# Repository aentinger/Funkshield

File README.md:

💾 Funkshield
==============

# 📸 Image

# 📂 Description

The Radio Shield provides an easy way to enable wireless communication between two or more Arduinos. Additionally the Radioshield has a Childboard connector socket which allows the Radio Shield to be further upgraded with sensors/actuators, e.g. a gas sensor, temperature sensor or a relay switch. A possible application would be temperature monitoring of all rooms of a house/appartment and performing an efficient regulation of the heating based on the measured data. For an quick and easy start, a open source Arduino library with sample programs is available.

**Features**

* Enables easy wireless communication with other Arduinos
* Usage of the popular RFM12B HF-Transceiver
* Frequency range: 433 MHz ISM-Band
* Childboard-Base for integration of further LXRobotics Childboards (e.g. gas sensor, temperature sensor, relay switch)
* Antenna with 2dbi gain
* Output power is selectable in 3 db steps ranging from 0 dbm to -21 dbm
* Third-Party-Arduino Library available for control with example programms

# 🎥 [Video](images/funkshield_demo.mp4)

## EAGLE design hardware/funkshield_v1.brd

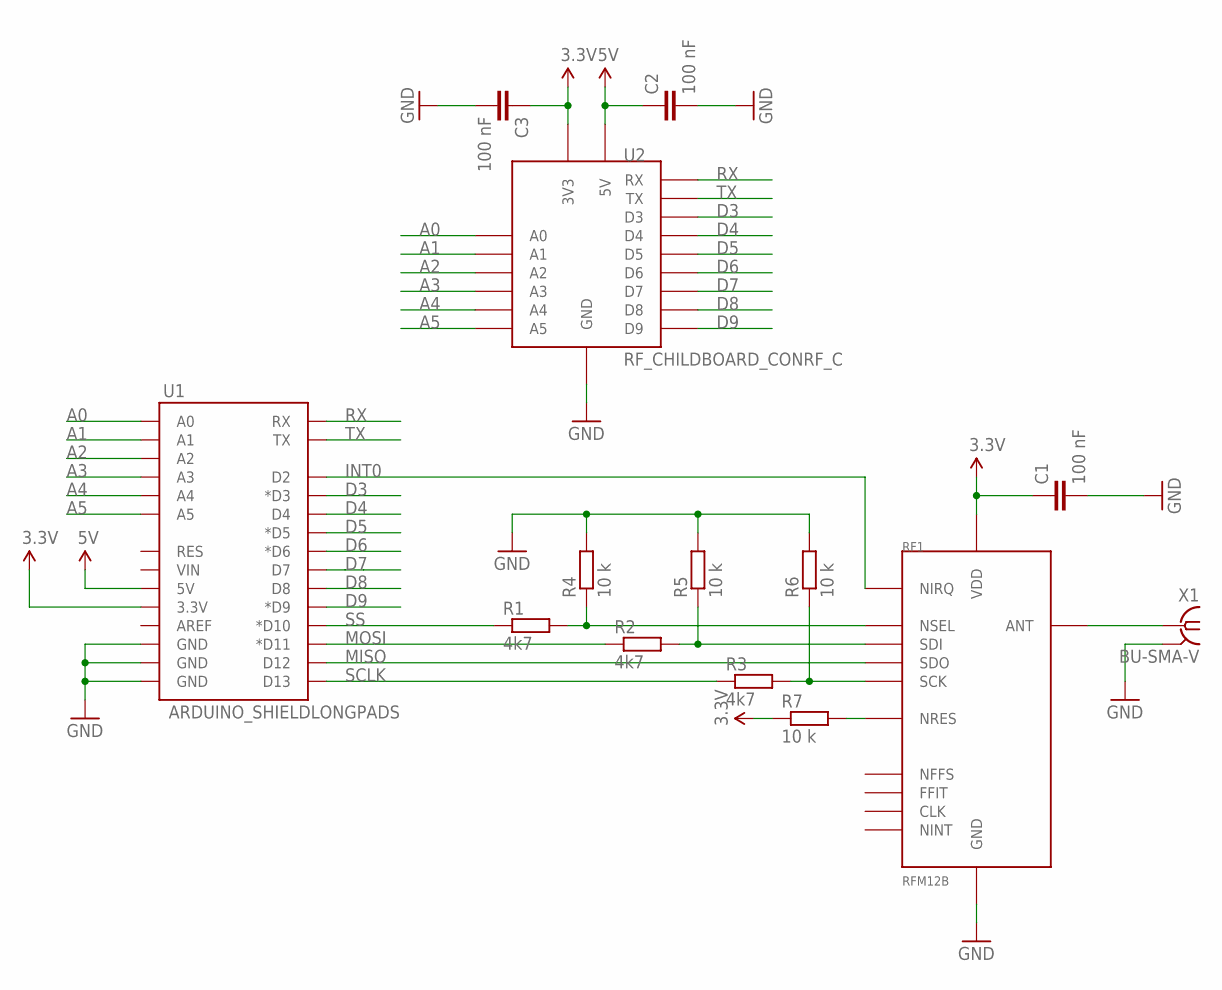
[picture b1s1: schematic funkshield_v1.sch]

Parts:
C1, C2, C3: 100 nF; C0805
R1, R2, R3: 4k7; M0805
R4, R5, R6, R7: 10 k; M0805
RF1: RFM12B
U1: ARDUINO_SHIELDLONGPADS; DUEMILANOVE_SHIELD_LONGPADS
U2: RF_CHILDBOARD_CONRF_C; RF_CHILDBOARD_CON
X1: BU-SMA-V

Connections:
3.3V: C1.1, C3.1, R7.1, RF1.VDD, U1.3.3V, U2.3V3
5V: C2.1, U1.5V, U2.5V
A0: U1.A0, U2.A0
A1: U1.A1, U2.A1
A2: U1.A2, U2.A2
A3: U1.A3, U2.A3
A4: U1.A4, U2.A4
A5: U1.A5, U2.A5
D3: U1.D3 (*D3), U2.D3
D4: U1.D4, U2.D4
D5: U1.D5 (*D5), U2.D5
D6: U1.D6 (*D6), U2.D6
D7: U1.D7, U2.D7
D8: U1.D8, U2.D8
D9: U1.D9 (*D9), U2.D9
GND: C1.2, C2.2, C3.2, R4.2, R5.2, R6.2, RF1.GND, RF1.GND1 (GND), U1.GND@0 (GND), U1.GND@1 (GND), U1.GND@2 (GND), U2.GND, U2.GND1 (GND), U2.GND2 (GND), X1.2 (GND), X1.3 (GND), X1.4 (GND), X1.5 (GND)
INT0: RF1.NIRQ, U1.D2
MISO: RF1.SDO, U1.D12
MOSI: R2.1, U1.D11 (*D11)
unnamed: R1.2, R4.1, RF1.NSEL
unnamed: R2.2, R5.1, RF1.SDI
unnamed: R3.2, R6.1, RF1.SCK
unnamed: R7.2, RF1.NRES
unnamed: RF1.ANT, X1.1
RX: U1.RX, U2.RX
SCLK: R3.1, U1.D13
SS: R1.1, U1.D10 (*D10)
TX: U1.TX, U2.TX

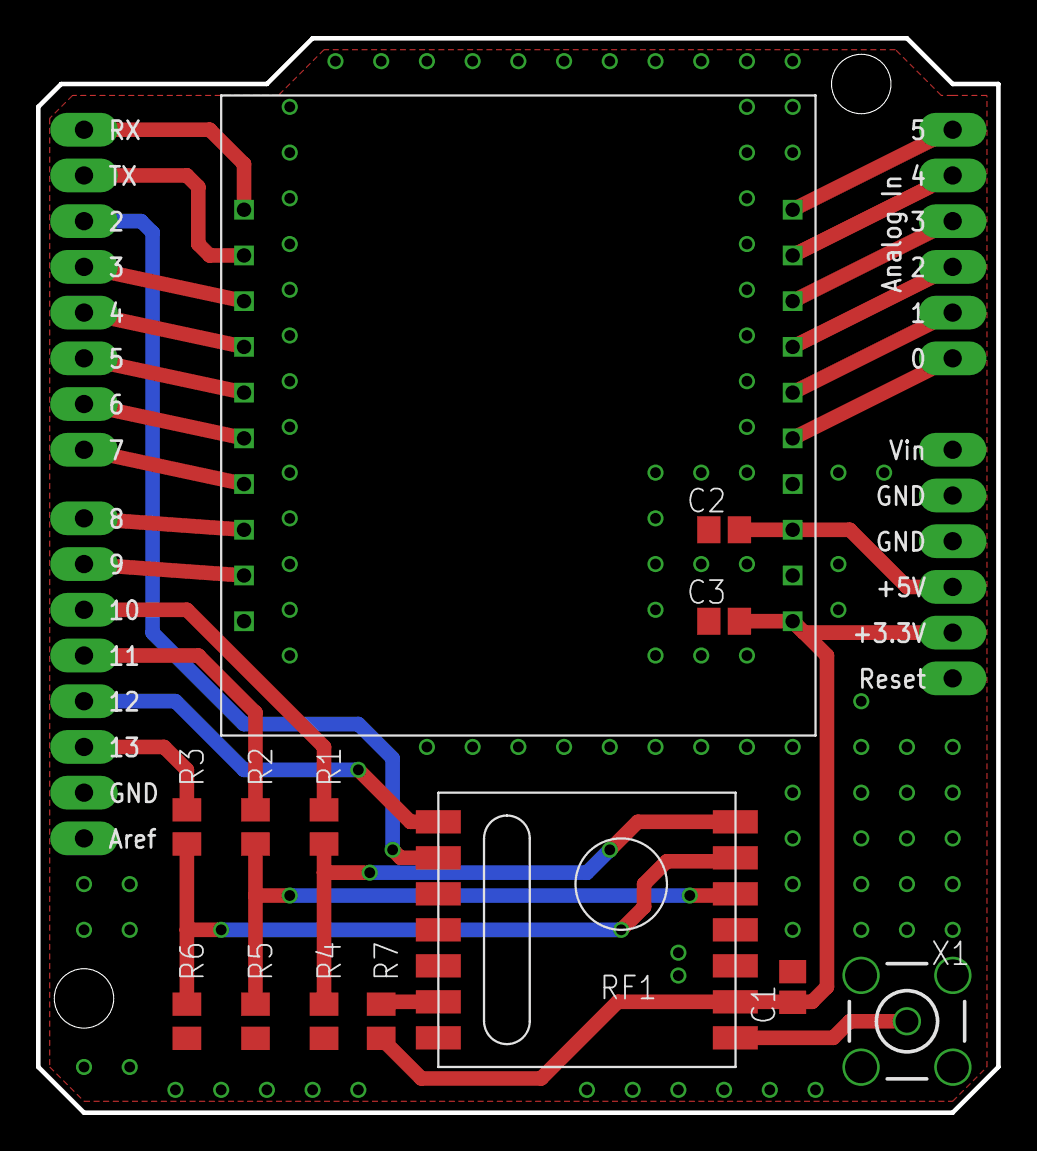
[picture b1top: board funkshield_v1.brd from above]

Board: 2 copper layers, 53.3 x 59.7 mm, 14 parts (0 on the bottom side), 28 nets.

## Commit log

2014-01-15 initial checkin for funkshield
2014-06-11 adding gas warning system demo
2015-12-27 created folder for demo sketch file gas_warning_system_radio.ino
2017-06-27 Adding hardware + images
2025-03-26 Add BOM.
2025-03-26 Upload demo video.
2025-03-26 Pretty up README.

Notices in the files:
README.md:
License: CC BY-NC-SA 4.0
hardware/funkshield_v1.sch:
Copyright by Alexander Entinger, MSc / LXRobotics GmbH
CC BY-NC-SA 3.0 (http://creativecommons.org/licenses/by-nc-sa/3.0/)
parts and their libraries:
SparkFun-Boards: Licensing: CC v3.0 Share-Alike You are welcome to use this library for commercial purposes.
